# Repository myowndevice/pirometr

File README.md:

## Пирометр

Компактный пирометр — точное измерение температуры поверхности на расстоянии. Размер — всего 3см на 4 см. Питание от аккумулятора, более 300 измерений на одном заряде. Расстояние измерения до 50cм, угол рассеивания 10 градусов. Измерение температуры в широком диапазоне от +300 до -100 градусов. Яркий светодиодный индикатор. Автоматическое отключение через 30 секунд для экономии энергии. Измерение температуры чая или молока, воды в ванной, поверхности моря, воздуха на улице, компонентов на плате.
Ключевые параметры самодельного пирометра:
- Компактный размер
- Питание от аккумулятора, длительная работа от одного заряда — более 300 измерений на одном заряде
- Измерение температуры поверхности на расстоянии в широком диапазоне от -40 до 400 градусов
- Автоматическое выключение через 30 секунд для экономии заряда
- Микроконтроллерное управление на базе STM8

Данный репозитарий содержит все необходимые файлы для изготовления велокомпьютера.Если вы будете скачивать файлы через web не забудьте скачать общую папку Kicadlib.

Ознакомится со схемой и подробным описанием пирометра, программы, и порядка сборки можно, [прочитав эту подробную статью](http://myowndevice.ru/index.php/pribory/home/item/50-mini-pirometr)

Также [здесь](http://myowndevice.ru) вы найдете подробное описание как сделать другие приборы, много теории о том, как их делать, методику изготовления печатных плат и много другого.

Изучай микроконтроллеры, делай платы дома, разрабатывай электронику сам!

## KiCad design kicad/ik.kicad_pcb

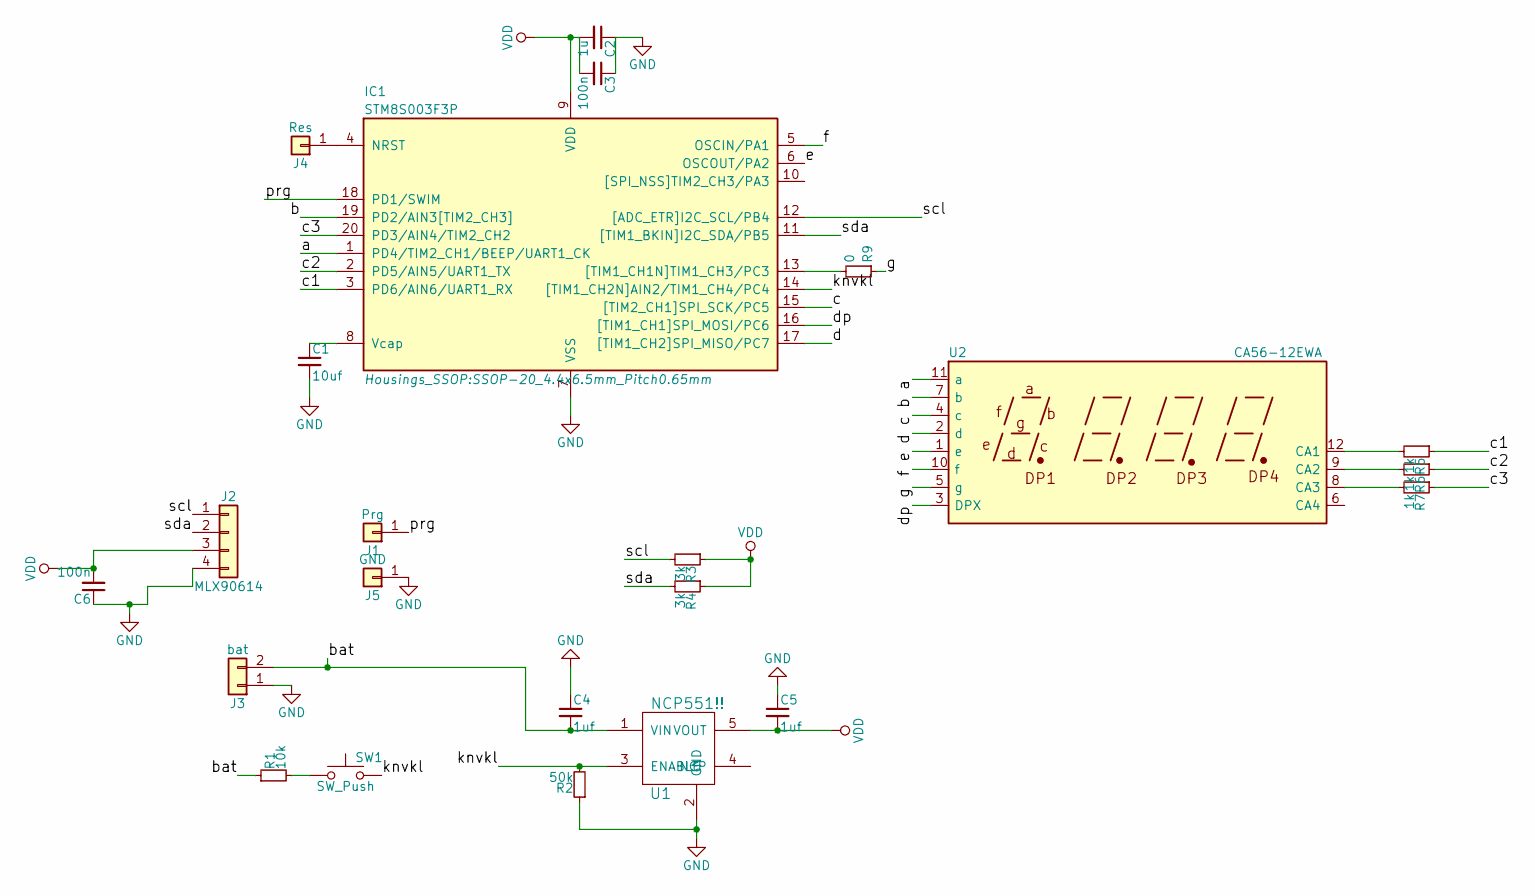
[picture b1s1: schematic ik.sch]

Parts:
C1: 10uf; C_0805_HandSoldering
C2: 1u; C_0805_HandSoldering
C3, C6: 100n; C_0603_HandSoldering
C4, C5: 1uf; C_0805_HandSoldering
IC1: STM8S003F3P; SSOP-20_4.4x6.5mm_Pitch0.65mm
J1: Prg; wirepad_mini
J2: MLX90614; MLX90615
J3: bat; Pin_Header_Angled_1x02_Pitch2.54mm
J4: Res; wirepad_mini
J5: GND; wirepad_mini
R1: 10k; R_0603_HandSoldering
R2: 50k; R_0603_HandSoldering
R3, R4: 3k; R_0603_HandSoldering
R5, R6, R7: 1k; R_0603_HandSoldering
R9: 0; R_0603_HandSoldering
SW1: SW_Push; SW_Tactile_SPST_Angled_PTS645Vx58-2LFS
U1: NCP551!!; SOT-23-5_HandSoldering
U2: CA56-12EWA; indicator_3cif

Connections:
/a: IC1.1 (PD4/TIM2_CH1/BEEP/UART1_CK), U2.11 (a)
/b: IC1.19 (PD2/AIN3[TIM2_CH3]), U2.7 (b)
/bat: C4.2, J3.2, R1.1, U1.1 (VIN)
/c: IC1.15 ([TIM2_CH1]SPI_SCK/PC5), U2.4 (c)
/c1: IC1.3 (PD6/AIN6/UART1_RX), R5.1
/c2: IC1.2 (PD5/AIN5/UART1_TX), R6.1
/c3: IC1.20 (PD3/AIN4/TIM2_CH2), R7.1
/d: IC1.17 ([TIM1_CH2]SPI_MISO/PC7), U2.2 (d)
/dp: IC1.16 ([TIM1_CH1]SPI_MOSI/PC6), U2.3 (DPX)
/e: IC1.6 (OSCOUT/PA2), U2.1 (e)
/f: IC1.5 (OSCIN/PA1), U2.10 (f)
/g: R9.1, U2.5 (g)
/knvkl: IC1.14 ([TIM1_CH2N]AIN2/TIM1_CH4/PC4), R2.2, SW1.2, U1.3 (ENABLE)
/prg: IC1.18 (PD1/SWIM), J1.1
/scl: IC1.12 ([ADC_ETR]I2C_SCL/PB4), J2.1, R3.2
/sda: IC1.11 ([TIM1_BKIN]I2C_SDA/PB5), J2.2, R4.2
GND: C1.2, C2.1, C3.1, C4.1, C5.1, C6.1, IC1.7 (VSS), J2.4, J3.1, J5.1, R2.1, U1.2 (GND)
unnamed: C1.1, IC1.8 (Vcap)
unnamed: IC1.4 (NRST), J4.1
unnamed: IC1.13 ([TIM1_CH1N]TIM1_CH3/PC3), R9.2
unnamed: R1.2, SW1.1
unnamed: R5.2, U2.12 (CA1)
unnamed: R6.2, U2.9 (CA2)
unnamed: R7.2, U2.8 (CA3)
VDD: C2.2, C3.2, C5.2, C6.2, IC1.9 (VDD), J2.3, R3.1, R4.1, U1.5 (VOUT)

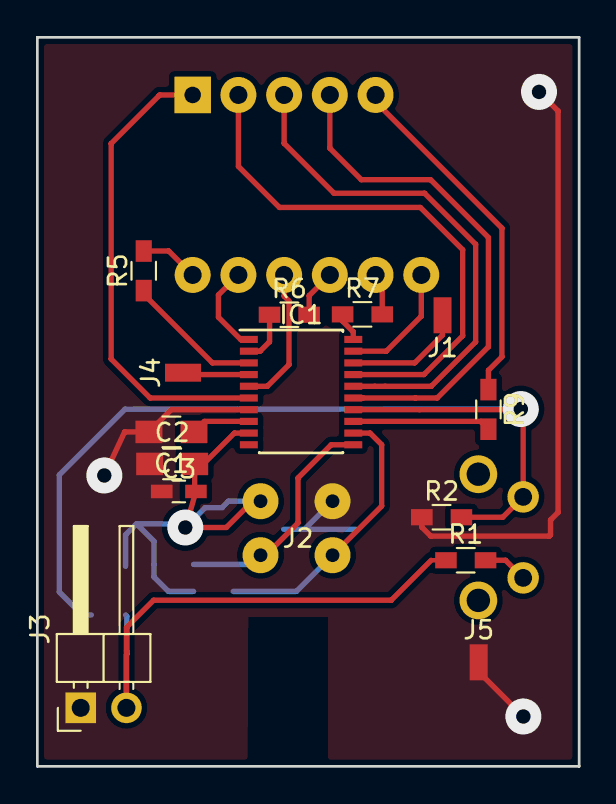
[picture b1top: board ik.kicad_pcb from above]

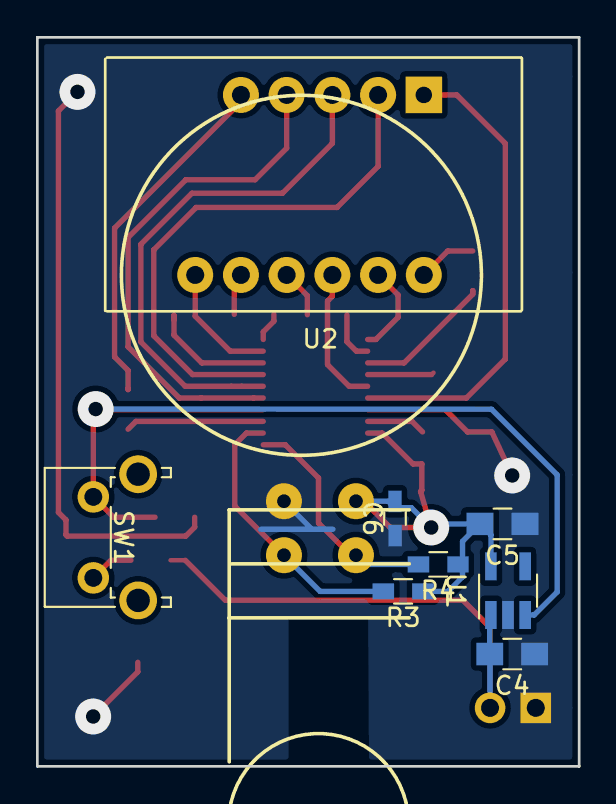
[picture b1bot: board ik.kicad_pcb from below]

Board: 2 copper layers, 30.1 x 40.5 mm, 23 parts (8 on the bottom side), 25 nets.

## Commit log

2020-12-18 start
